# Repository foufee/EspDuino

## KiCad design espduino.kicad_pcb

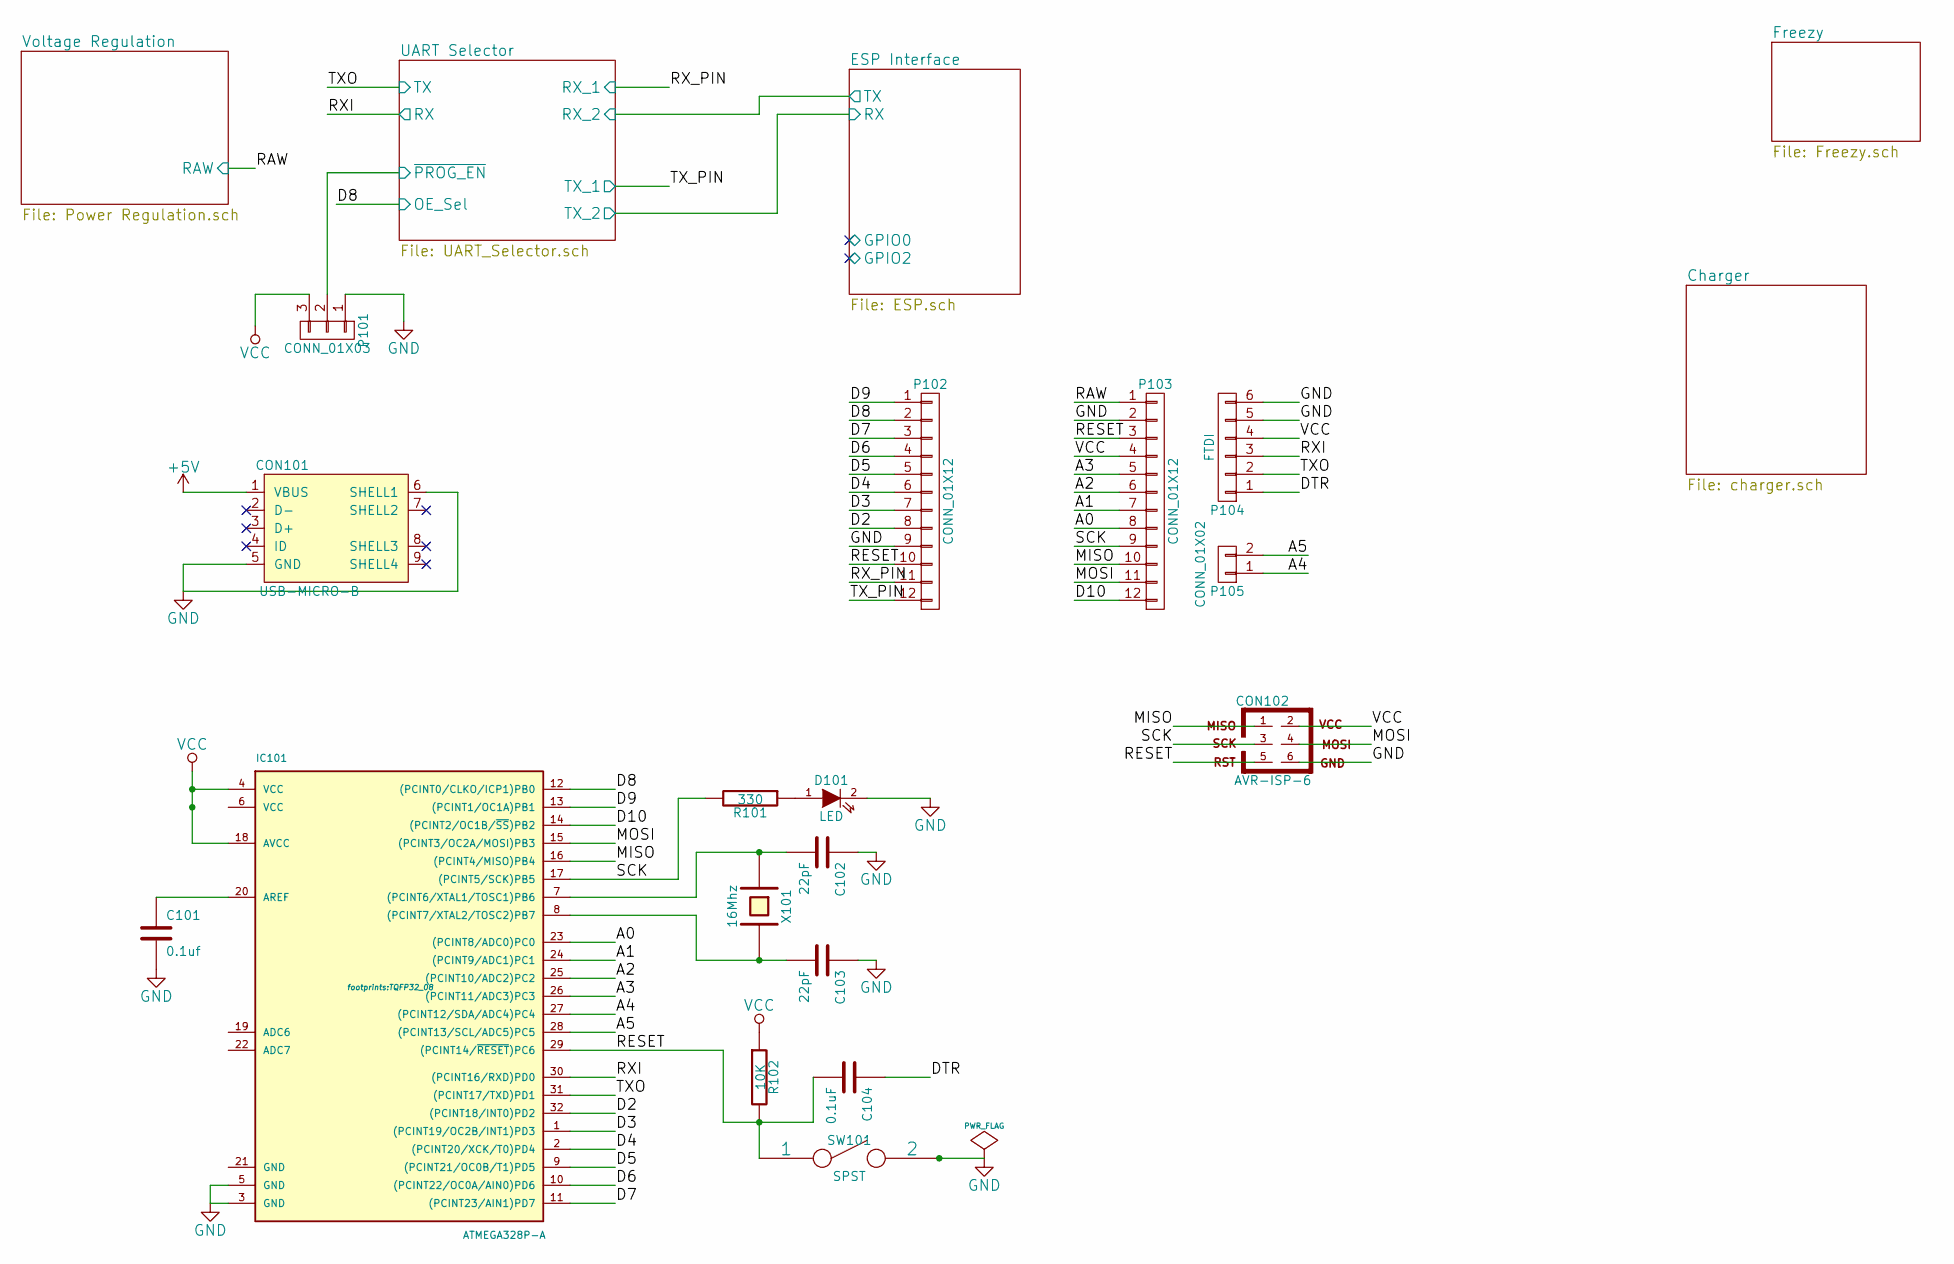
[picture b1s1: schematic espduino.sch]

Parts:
C101: 0.1uf; C_0805
C102, C103: 22pF; C_0805
C104: 0.1uF; C_0805
CON101: USB-MICRO-B; USB_Micro-B
CON102: AVR-ISP-6; Pin_Header_Straight_2x03
D101: LED; LED-0805
IC101: ATMEGA328P-A; TQFP32_08
P101: CONN_01X03; Pin_Header_Straight_1x03
P102, P103: CONN_01X12; Pin_Header_Straight_1x12
P104: FTDI; Pin_Header_Angled_1x06
P105: CONN_01X02; Pin_Header_Straight_1x02
R101: 330; R_0805
R102: 10K; R_0805
SW101: SPST; 4x4_Tactile_SMD_switch
X101: 16Mhz; Crystal_HC49-SD_SMD

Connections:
/A0: IC101.23 ((PCINT8/ADC0)PC0), P103.8
/A1: IC101.24 ((PCINT9/ADC1)PC1), P103.7
/A2: IC101.25 ((PCINT10/ADC2)PC2), P103.6
/A3: IC101.26 ((PCINT11/ADC3)PC3), P103.5
/A4: IC101.27 ((PCINT12/SDA/ADC4)PC4), P105.1
/A5: IC101.28 ((PCINT13/SCL/ADC5)PC5), P105.2
/D2: IC101.32 ((PCINT18/INT0)PD2), P102.8
/D3: IC101.1 ((PCINT19/OC2B/INT1)PD3), P102.7
/D4: IC101.2 ((PCINT20/XCK/T0)PD4), P102.6
/D5: IC101.9 ((PCINT21/OC0B/T1)PD5), P102.5
/D6: IC101.10 ((PCINT22/OC0A/AIN0)PD6), P102.4
/D7: IC101.11 ((PCINT23/AIN1)PD7), P102.3
/D9: IC101.13 ((PCINT1/OC1A)PB1), P102.1
/D10: IC101.14 ((PCINT2/OC1B/~SS~)PB2), P103.12
/DTR: C104.1, P104.1
/MISO: CON102.1, IC101.16 ((PCINT4/MISO)PB4), P103.10
/MOSI: CON102.4, IC101.15 ((PCINT3/OC2A/MOSI)PB3), P103.11
/RESET: C104.2, CON102.5, IC101.29 ((PCINT14/~RESET~)PC6), P102.10, P103.3, R102.2, SW101.1
/SCK: CON102.3, IC101.17 ((PCINT5/SCK)PB5), P103.9, R101.2
/UART Selector/OE_Sel: IC101.12 ((PCINT0/CLKO/ICP1)PB0), P102.2; also elsewhere on the board
/UART Selector/RX: IC101.30 ((PCINT16/RXD)PD0), P104.3; also elsewhere on the board
/UART Selector/RX_1: P102.11; also elsewhere on the board
/UART Selector/TX: IC101.31 ((PCINT17/TXD)PD1), P104.2; also elsewhere on the board
/UART Selector/TX_1: P102.12; also elsewhere on the board
/UART Selector/~PROG_EN: P101.2; also elsewhere on the board
/Voltage Regulation/RAW: P103.1; also elsewhere on the board
GND: C101.2, C102.1, C103.1, CON101.5 (GND), CON101.6 (SHELL1), CON102.6, D101.2 (K), IC101.3 (GND), IC101.5 (GND), P101.1, P102.9, P103.2, P104.5, P104.6, SW101.2; also elsewhere on the board
unnamed: C101.1, IC101.20 (AREF)
unnamed: C102.2, IC101.7 ((PCINT6/XTAL1/TOSC1)PB6), X101.1
unnamed: C103.2, IC101.8 ((PCINT7/XTAL2/TOSC2)PB7), X101.2
unnamed: D101.1 (A), R101.1
VCC: CON101.1 (VBUS), CON102.2, IC101.4 (VCC), IC101.18 (AVCC), P101.3, P103.4, P104.4, R102.1; also elsewhere on the board

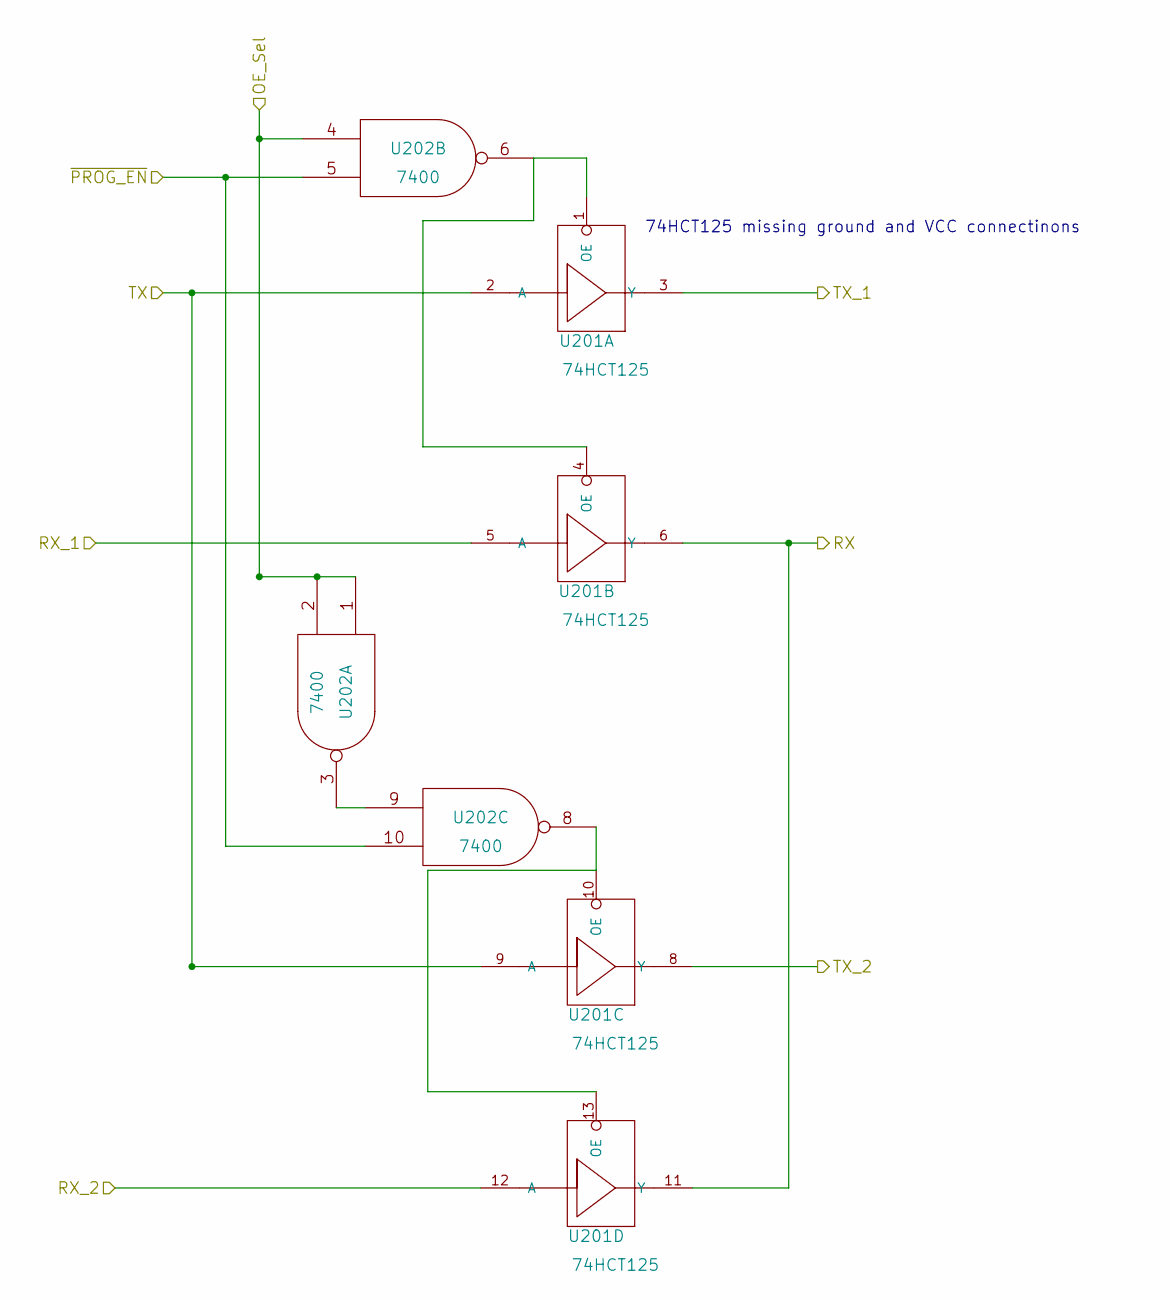
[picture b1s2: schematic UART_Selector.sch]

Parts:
U201: 74HCT125; SOIC-14_N
U202: 7400; SOIC-14_N

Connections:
/ESP Interface/RX: U201.8 (Y); also elsewhere on the board
/UART Selector/OE_Sel: U202.1, U202.2, U202.4; also elsewhere on the board
/UART Selector/RX: U201.6 (Y), U201.11 (Y); also elsewhere on the board
/UART Selector/RX_1: U201.5 (A); also elsewhere on the board
/UART Selector/RX_2: U201.12 (A); also elsewhere on the board
/UART Selector/TX: U201.2 (A), U201.9 (A); also elsewhere on the board
/UART Selector/TX_1: U201.3 (Y); also elsewhere on the board
/UART Selector/~PROG_EN: U202.5, U202.10; also elsewhere on the board
GND: U202.7 (GND); also elsewhere on the board
unnamed: U201.1 (OE), U201.4 (OE), U202.6
unnamed: U201.10 (OE), U201.13 (OE), U202.8
unnamed: U202.3, U202.9
VCC: U202.14 (VCC); also elsewhere on the board

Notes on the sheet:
74HCT125 missing ground and VCC connectinons

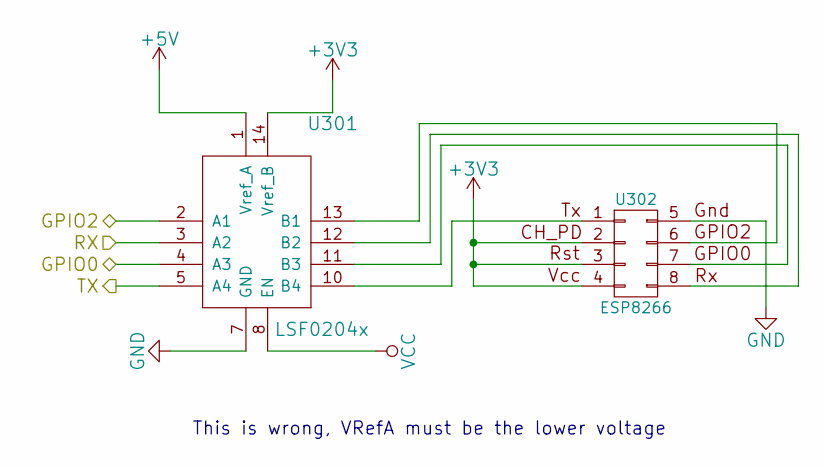
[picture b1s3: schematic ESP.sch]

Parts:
U301: LSF0204x; AB2_TSSOP14
U302: ESP8266; ESP8266_2

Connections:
+3V3: U301.14 (Vref_B), U302.2 (CH_PD), U302.3 (RST), U302.4 (VCC); also elsewhere on the board
/ESP Interface/RX: U301.3 (A2); also elsewhere on the board
/UART Selector/RX_2: U301.5 (A4); also elsewhere on the board
GND: U301.7 (GND), U302.5 (GND); also elsewhere on the board
unnamed: U301.10 (B4), U302.1 (TX)
unnamed: U301.11 (B3), U302.7 (P6)
unnamed: U301.12 (B2), U302.8
unnamed: U301.13 (B1), U302.6 (P4)
VCC: U301.1 (Vref_A), U301.8 (EN); also elsewhere on the board

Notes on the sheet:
This is wrong, VRefA must be the lower voltage

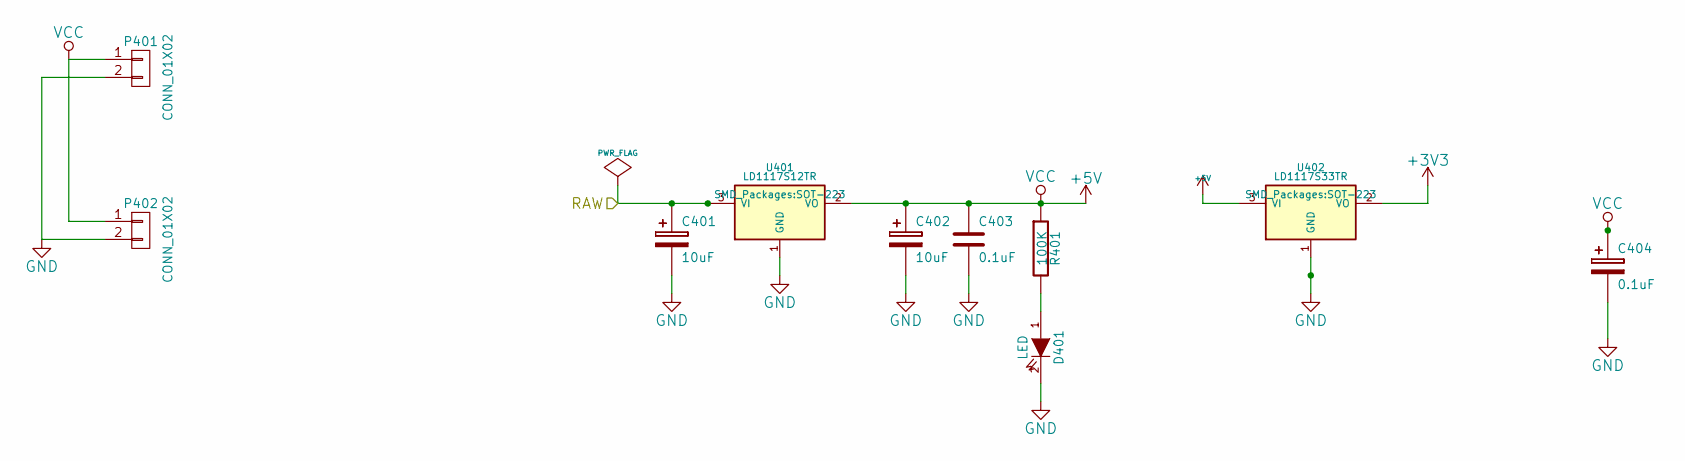
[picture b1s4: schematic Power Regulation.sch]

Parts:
C401, C402: 10uF; c_elec_4x5.8
C403, C404: 0.1uF; C_0805
D401: LED; LED-0805
P401, P402: CONN_01X02; Pin_Header_Straight_1x02
R401: 100K; R_0805_HandSoldering
U401: LD1117S12TR; SOT-223
U402: LD1117S33TR; SOT-223

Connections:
+3V3: U402.2 (VO); also elsewhere on the board
/Voltage Regulation/RAW: C401.1, U401.3 (VI); also elsewhere on the board
GND: C401.2, C402.2, C403.2, C404.2, D401.2 (K), P401.2, P402.2, U401.1 (GND), U402.1 (GND); also elsewhere on the board
unnamed: D401.1 (A), R401.2
VCC: C402.1, C403.1, C404.1, P401.1, P402.1, R401.1, U401.2 (VO), U402.3 (VI); also elsewhere on the board

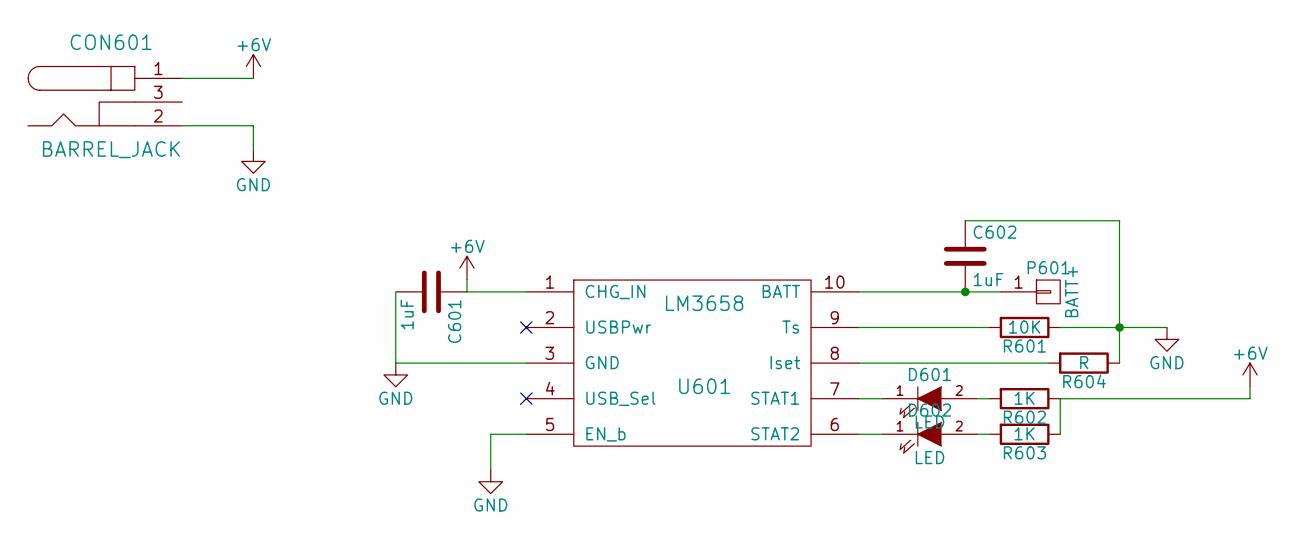
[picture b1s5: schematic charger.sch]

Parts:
C601, C602: 1uF; C_0805
CON601: BARREL_JACK
D601, D602: LED; LED-0805
P601: BATT+; Pin_Header_Straight_1x01
R601: 10K; R_0805
R602, R603: 1K; R_0805
R604: R; R_0805
U601: LM3658; WSON10

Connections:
+6V: C601.1, CON601.1, R602.1, R603.1, U601.1 (CHG_IN)
GND: C601.2, C602.1, CON601.2, R601.1, R604.1, U601.3 (GND), U601.5 (EN_b); also elsewhere on the board
unnamed: C602.2, P601.1, U601.10 (BATT)
unnamed: D601.1 (K), U601.7 (STAT1)
unnamed: D601.2 (A), R602.2
unnamed: D602.1 (K), U601.6 (STAT2)
unnamed: D602.2 (A), R603.2
unnamed: R601.2, U601.9 (Ts)
unnamed: R604.2, U601.8 (Iset)

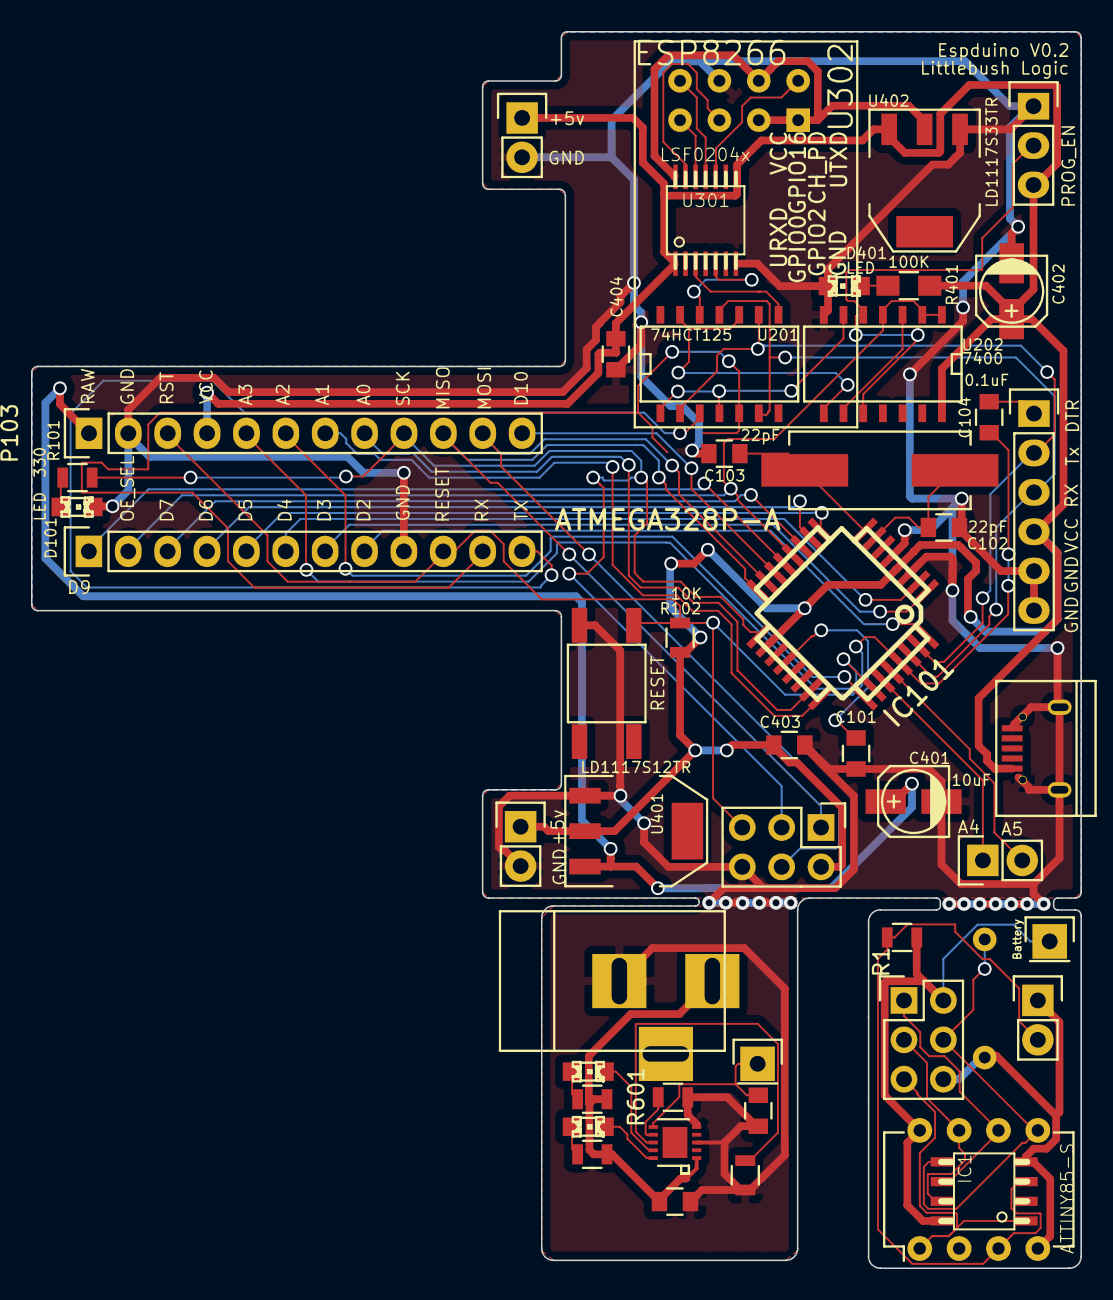
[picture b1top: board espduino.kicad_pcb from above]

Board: 2 copper layers, 67.7 x 79.8 mm, 49 parts (1 on the bottom side), 57 nets.

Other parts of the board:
BT1: Battery; Pin_Header_Straight_1x01
CON1: AVR-ISP-6; Pin_Header_Straight_2x03
IC1: ATTINY85-S; AB2_SO08
IC2: ATTINY85-P; DIP-8_W7.62mm
P1: CONN_01X02; Pin_Header_Straight_1x02
R1: R; R_0805
SP1: SPEAKER; buzzer

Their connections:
/Freezy/ADC: IC1.3, IC2.3, P1.2, R1.2
/Freezy/MISO: CON1.1, IC1.6, IC2.6
/Freezy/MOSI: CON1.4, IC1.5, IC2.5, SP1.2
/Freezy/SCK: CON1.3, IC1.7, IC2.7
/Freezy/~RST: CON1.5, IC1.1, IC2.1
GND: CON1.6, IC1.4, IC2.4, P1.1, SP1.1; also elsewhere on the board
unnamed: BT1.1, CON1.2, IC1.8, IC2.8, R1.1

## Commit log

2015-04-23 Initial
2015-04-27 Redesign the board and add USB
2015-06-29 Add mechanism to disable UART selector
2015-06-29 Issue #4 RAW goes through LDO, +5v from USB doesn't
2015-06-29 Fix pin for ESP
2015-07-13 More fixes
2015-08-05 Version 0.2
2015-08-26 Minor changes
